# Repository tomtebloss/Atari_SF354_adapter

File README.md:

<h1 align="center">
PCB for use in an Atari SF354/314 case.
</h1>

<h2 align="center">
Exchange original pcb to be able to read double sided floppy.

---

</h2>

---

## Background  

I bought an old SF354 case with a broken (dried belt) single sided floppy drive to convert to gotek. The case was the big eject button version. Apparently there is (at least) two different version of the pcb inside. One can be used with double sided drives without modifications. And one with a lot of components on the pcb that needs modifications to work with double sided drives (the one I got). I didn't get any signal cable or power cable/brick with my SF354 so it was no meaning to modify the old pcb since I had to source a power cable for it in that case. So I did a new PCB instead and used USB-C to power it. Only 5V. No 12V is used on this board. 

---

## What you will need  

- One Adapter PCB. Order with the [gerber] file "SF354_adapter_pcb_gerber_v1.5.zip" from your favorite PCB manufactory. 
- 1 or 2 pcs of BERG 4 pin floppy power connector (or solder the wires directly to the pcb).
- 1 or 2 pcs of 100nF (0,1uF) 0805 SMD capacitors. This can bew omitted if you want.
- 1 or 2 pcs of 1uF capacitors. Either SMD (1206) or through hole (5,12mm leg pitch).
- One 47uF electrolytic capacitor. Either SMD (size C. 6,3x7,7mm) or through hole (5mm leg pitch).
- 2 pcs of 14 pin DIN connectors. Desolder from old pcb (only one is needed).
- One 34 pin IDC connector. (or solder the wires directly to the pcb).
- One USB-C 6 pin SMD connector. Only used for power.
- One switch (SPDT) or small piece of wire if you don't use it. 
- One Gotek drive or a real disk drive. If Gotek is used you must remove motor on jumper (MO). Only S0 should be jumpered.
- One 3D printed [bracket] for Gotek pcb. 

BOM/partlist can also be found in the [gerber] zip. There is also [PDF] for some parts.

---

## How to

| Start by desoldering the two 14 pin DIN connectors from the old pcb. Solder the small capacitors on the new pcb. Choose whatever value you like. I did 1uF on the 1206 SMD ceramic capacitor and 0,1uF on the 0805 cap. Otherwise just do 1uF on the through hole if you don't like surface mount stuff. It doesn't matter really. Choose the placement closest to the connector you are going to use to power your drive. Solder in the USB-C connector. Then the 4 pin BERG connector for power. Choose a spot. Or solder wire directly to the board. You will need a female-female 4-pin power cable if you soldered in a connector on the pcb. Then solder 34 pin IDC connector and then one large 47 uF electrolytic capacitor. Choose through hole or surface mount. Either is fine. Then one or two 14 pin DIN connector. You can solder the ribbon cable directly to the pcb instead of 34 pin connector or you will have to buy a 34-pin ribbon cable for floppy otherwise. |    |
| :--- | :---: |
| I choose a switch and solder some wires and drilled, saw and filed some parts from the old gotek case. Square part goes inside of case (pic taken before I realized that I needed hole for USB connector). Small disc in the hole then large disc then switch. It will be a sandwich with the case in the middle. If you don't want a switch you have to solder a small wire between the holes that says LINK. Otherwise you will not have power for your drive. |     |
| The 3D printed front panel has a hole for a 2x5mm LED. I desoldered the round one from the gotek pcb and solderd in some pinheaders instead. I then soldered some wires on a new LED. The orientation can easily be switched if it doesn't lit up. |     |
| Assemble everything. Fasten with screw. I also used a rotary encoder and a buzzer on my gotek. You can use whatever mod you like on yours. Check flashfloppy [hardware mods]. |  |
|  |  |

---

## Testing

I tested this with a Mega ST 1 upgraded to 4Mb and with a TSENG ET4000AX graphics card. I also used 256Kb roms (EmuTOS v1.3 and TOS v2.06). I used two Goteks in the picture below but I also tested with two real floppy disk drives. But it should work with any double sided drive and system I hope. Do ***NOT*** use MO jumper on the Gotek otherwise it will not work! Only use S0 jumper. I can't remember what USB charger I used. 1A should be fine.

---

PCB made by Daniel Guldkrans aka DoG in Eagle April 2025.

[PDF]: pdf/
[gerber]: gerber/SF354_adapter_pcb_gerber_v1.5.zip
[bracket]: https://www.thingiverse.com/thing:6960806
[hardware mods]: https://github.com/keirf/flashfloppy/wiki/Hardware-Mods

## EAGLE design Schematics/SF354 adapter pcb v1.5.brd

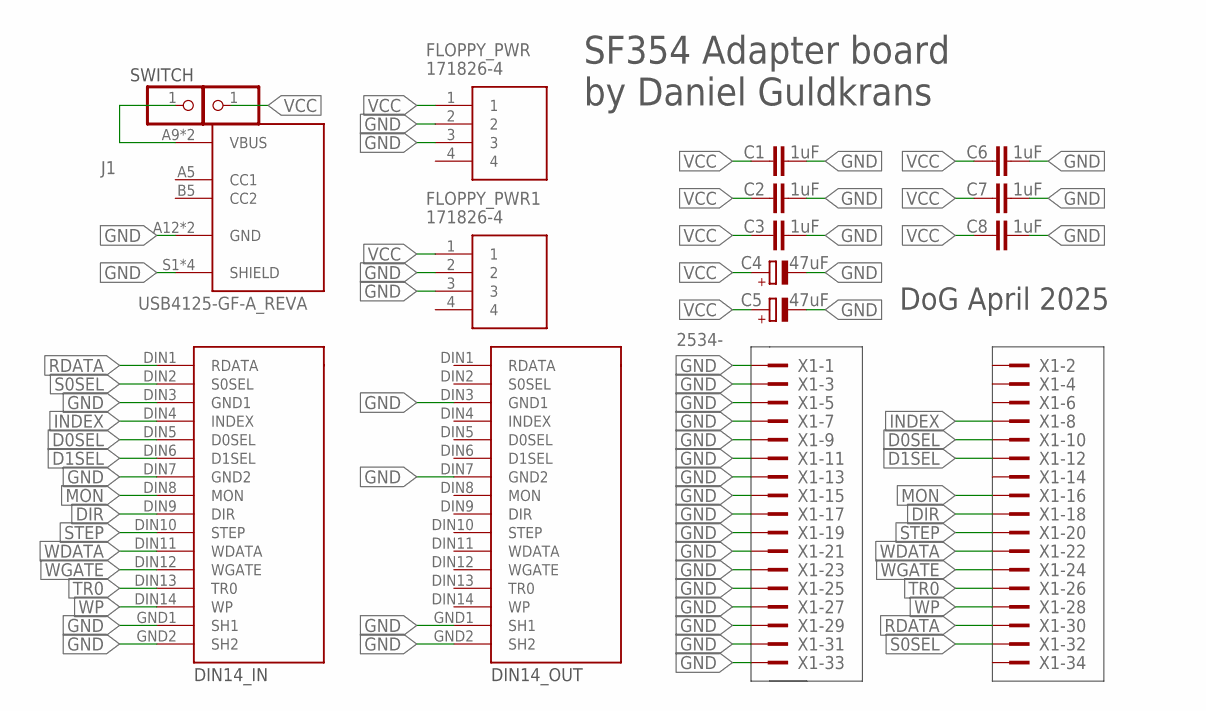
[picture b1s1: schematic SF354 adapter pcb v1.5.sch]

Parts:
C1, C6: 1uF; C1206
C2, C7: 1uF; C0805
C3, C8: 1uF; C050-025X075
C4: 47uF; UD-6,3X7,7_NICHICON
C5: 47uF; E5-10,5
FLOPPY_PWR, FLOPPY_PWR1: 171826-4; SHDRRA4W69P0X250_1X4_1000X1350
J1: USB4125-GF-A_REVA; GCT_USB4125-GF-A_REVA
JP1, JP2: PINHD-1X11X01_BH; 1X01_BH
U$1, U$2: DIN14
X1: 2534-; PAK100/2500-34

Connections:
D0SEL: U$1.DIN5 (D0SEL), X1.10
D1SEL: U$1.DIN6 (D1SEL), X1.12
DIR: U$1.DIN9 (DIR), X1.18
GND: C1.2, C2.2, C3.2, C4.-, C5.-, C6.2, C7.2, C8.2, FLOPPY_PWR.2, FLOPPY_PWR.3, FLOPPY_PWR1.2, FLOPPY_PWR1.3, J1.A12 (GND), J1.B12 (GND), J1.S1 (SHIELD), J1.S2 (SHIELD), J1.S3 (SHIELD), J1.S4 (SHIELD), U$1.DIN3 (GND1), U$1.DIN7 (GND2), U$1.GND1 (SH1), U$1.GND2 (SH2), U$2.DIN3 (GND1), U$2.DIN7 (GND2), U$2.GND1 (SH1), U$2.GND2 (SH2), X1.1, X1.3, X1.5, X1.7, X1.9, X1.11, X1.13, X1.15, X1.17, X1.19, X1.21, X1.23, X1.25, X1.27, X1.29, X1.31, X1.33
INDEX: U$1.DIN4 (INDEX), X1.8
MON: U$1.DIN8 (MON), X1.16
unnamed: J1.A9 (VBUS), J1.B9 (VBUS), JP2.1
RDATA: U$1.DIN1 (RDATA), X1.30
S0SEL: U$1.DIN2 (S0SEL), X1.32
STEP: U$1.DIN10 (STEP), X1.20
TR0: U$1.DIN13 (TR0), X1.26
VCC: C1.1, C2.1, C3.1, C4.+, C5.+, C6.1, C7.1, C8.1, FLOPPY_PWR.1, FLOPPY_PWR1.1, JP1.1
WDATA: U$1.DIN11 (WDATA), X1.22
WGATE: U$1.DIN12 (WGATE), X1.24
WP: U$1.DIN14 (WP), X1.28

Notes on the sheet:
DIN14_IN
DIN14_OUT
SWITCH
SF354 Adapter board by Daniel Guldkrans
DoG April 2025

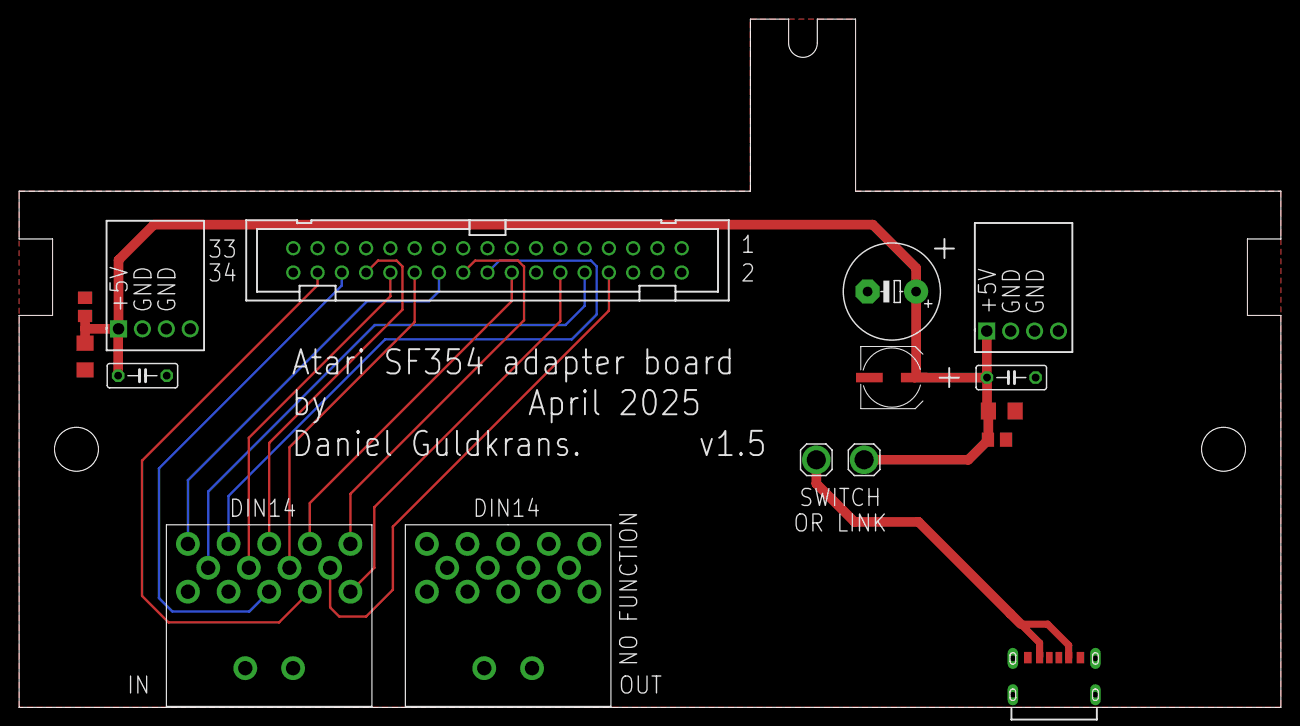
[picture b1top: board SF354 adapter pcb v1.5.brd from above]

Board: 2 copper layers, 132.0 x 72.0 mm, 16 parts (0 on the bottom side), 15 nets.

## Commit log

2025-05-12 PDF for parts
2025-05-12 gerber files for ordering pcb
2025-05-12 pics of all the stuff
2025-05-12 Read Me First!
2026-04-06 Exported pics from Eagle
2026-04-06 Eagle v9.6.2 files
2026-04-06 New knob, painted front, back covered
    New samller rotary knob, painted front, 2 soldered DIN14
2026-04-06 Painted front and activity LED
